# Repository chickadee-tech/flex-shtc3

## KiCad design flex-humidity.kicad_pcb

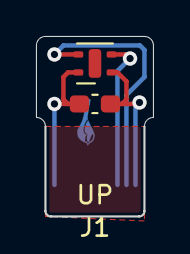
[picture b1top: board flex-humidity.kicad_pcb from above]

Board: 2 copper layers, 6.5 x 10.0 mm, 3 parts (0 on the bottom side), 4 nets.

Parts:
C1: 0.1uF; C_0603_1608Metric_Pad1.08x0.95mm_HandSolder
J1: 10POSFPC; 10pins-flex
U1: SHTC3; Sensirion_DFN-4-1EP_2x2mm_P1mm_EP0.7x1.6mm

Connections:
+3V3: C1.1, J1.10, U1.1
/SCL: J1.8, U1.2
/SDA: J1.9, U1.3
GND: C1.2, J1.1, U1.4

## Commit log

2021-02-15 v1 flex shtc3
